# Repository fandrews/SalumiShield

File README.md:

SalumiShield
============

Arduino shield for salumi controller

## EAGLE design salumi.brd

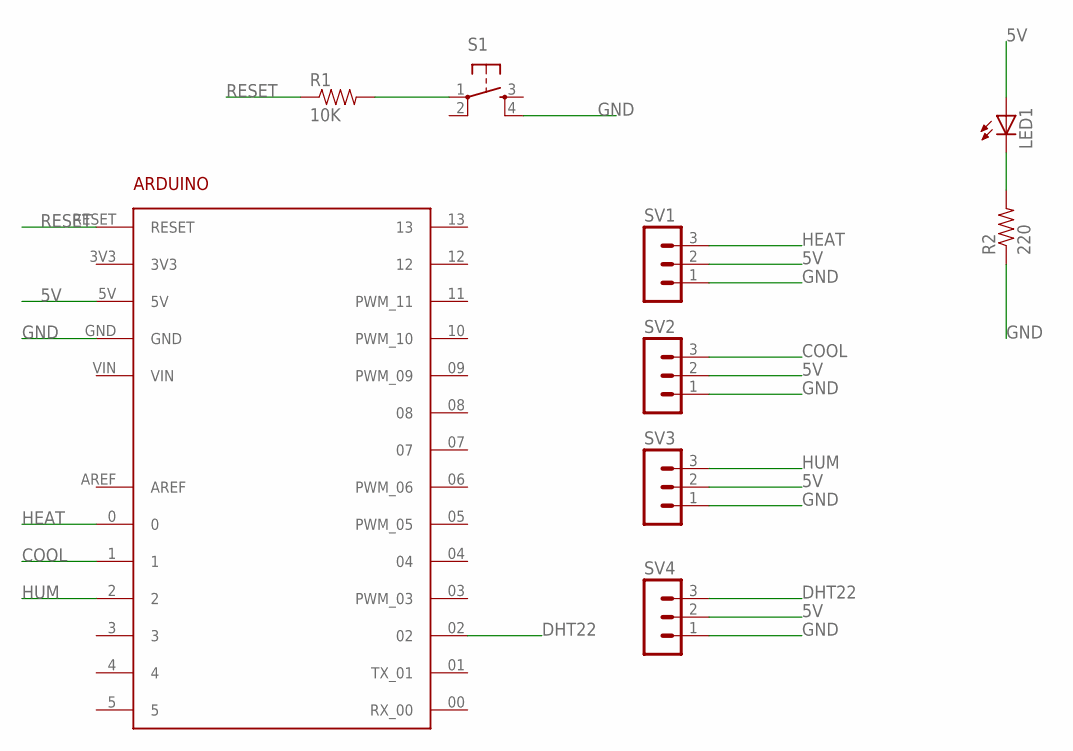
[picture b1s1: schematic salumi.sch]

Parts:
ARDUINO1: ARDUINO
LED1: LED5MM
R1: 10K; AXIAL-0.3
R2: 220; AXIAL-0.3
S1: TAC_SWITCHPTH; TACTILE-PTH
SV1, SV2, SV3, SV4: MA03-1

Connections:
5V: ARDUINO1.5V, LED1.A, SV1.2, SV2.2, SV3.2, SV4.2
COOL: ARDUINO1.1, SV2.3
DHT22: ARDUINO1.02, SV4.3
GND: ARDUINO1.GND, R2.P$1 (1), S1.4, SV1.1, SV2.1, SV3.1, SV4.1
HEAT: ARDUINO1.0, SV1.3
HUM: ARDUINO1.2, SV3.3
unnamed: R1.P$2 (2), S1.1
unnamed: LED1.K (C), R2.P$2 (2)
RESET: ARDUINO1.RESET, R1.P$1 (1)

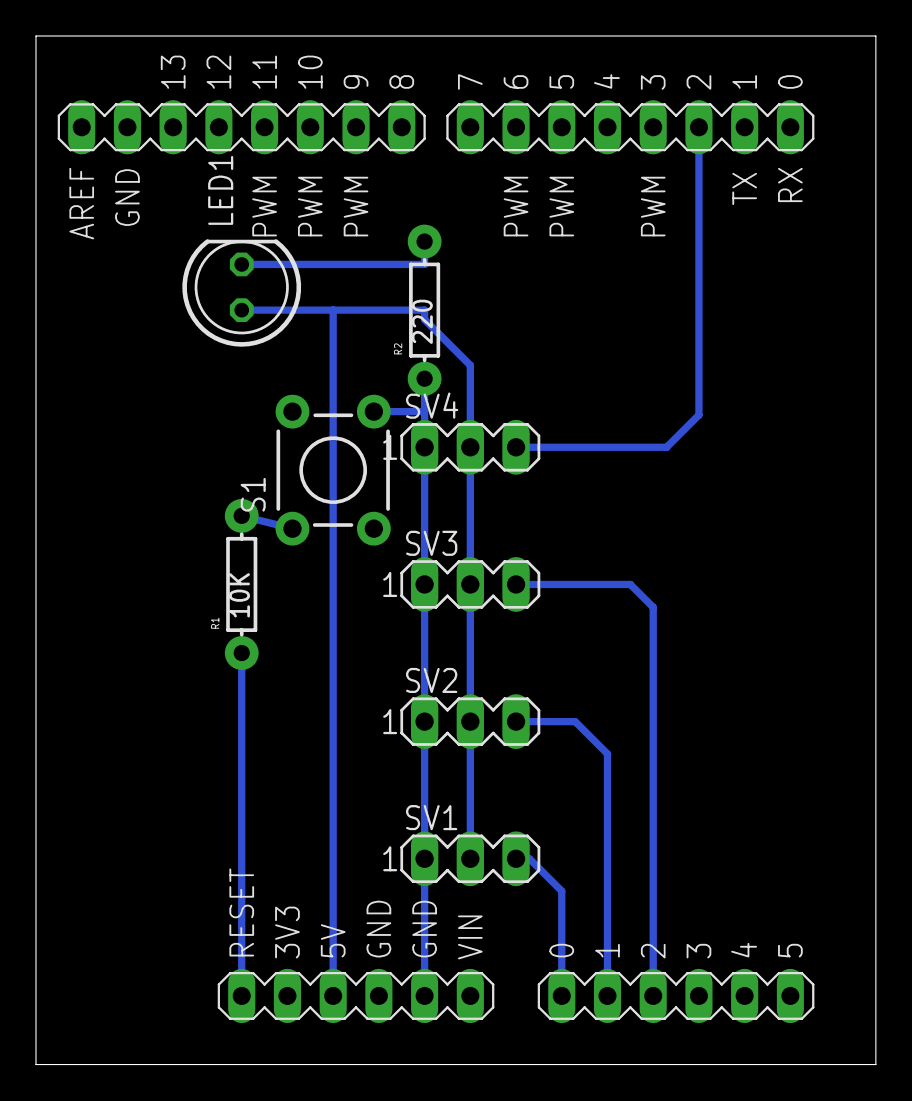
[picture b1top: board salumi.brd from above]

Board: 2 copper layers, 46.7 x 57.1 mm, 9 parts (0 on the bottom side), 9 nets.

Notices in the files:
parts and their libraries:
SparkFun-Electromechanical: Licensing: CC v3.0 Share-Alike You are welcome to use this library for commercial purposes.
